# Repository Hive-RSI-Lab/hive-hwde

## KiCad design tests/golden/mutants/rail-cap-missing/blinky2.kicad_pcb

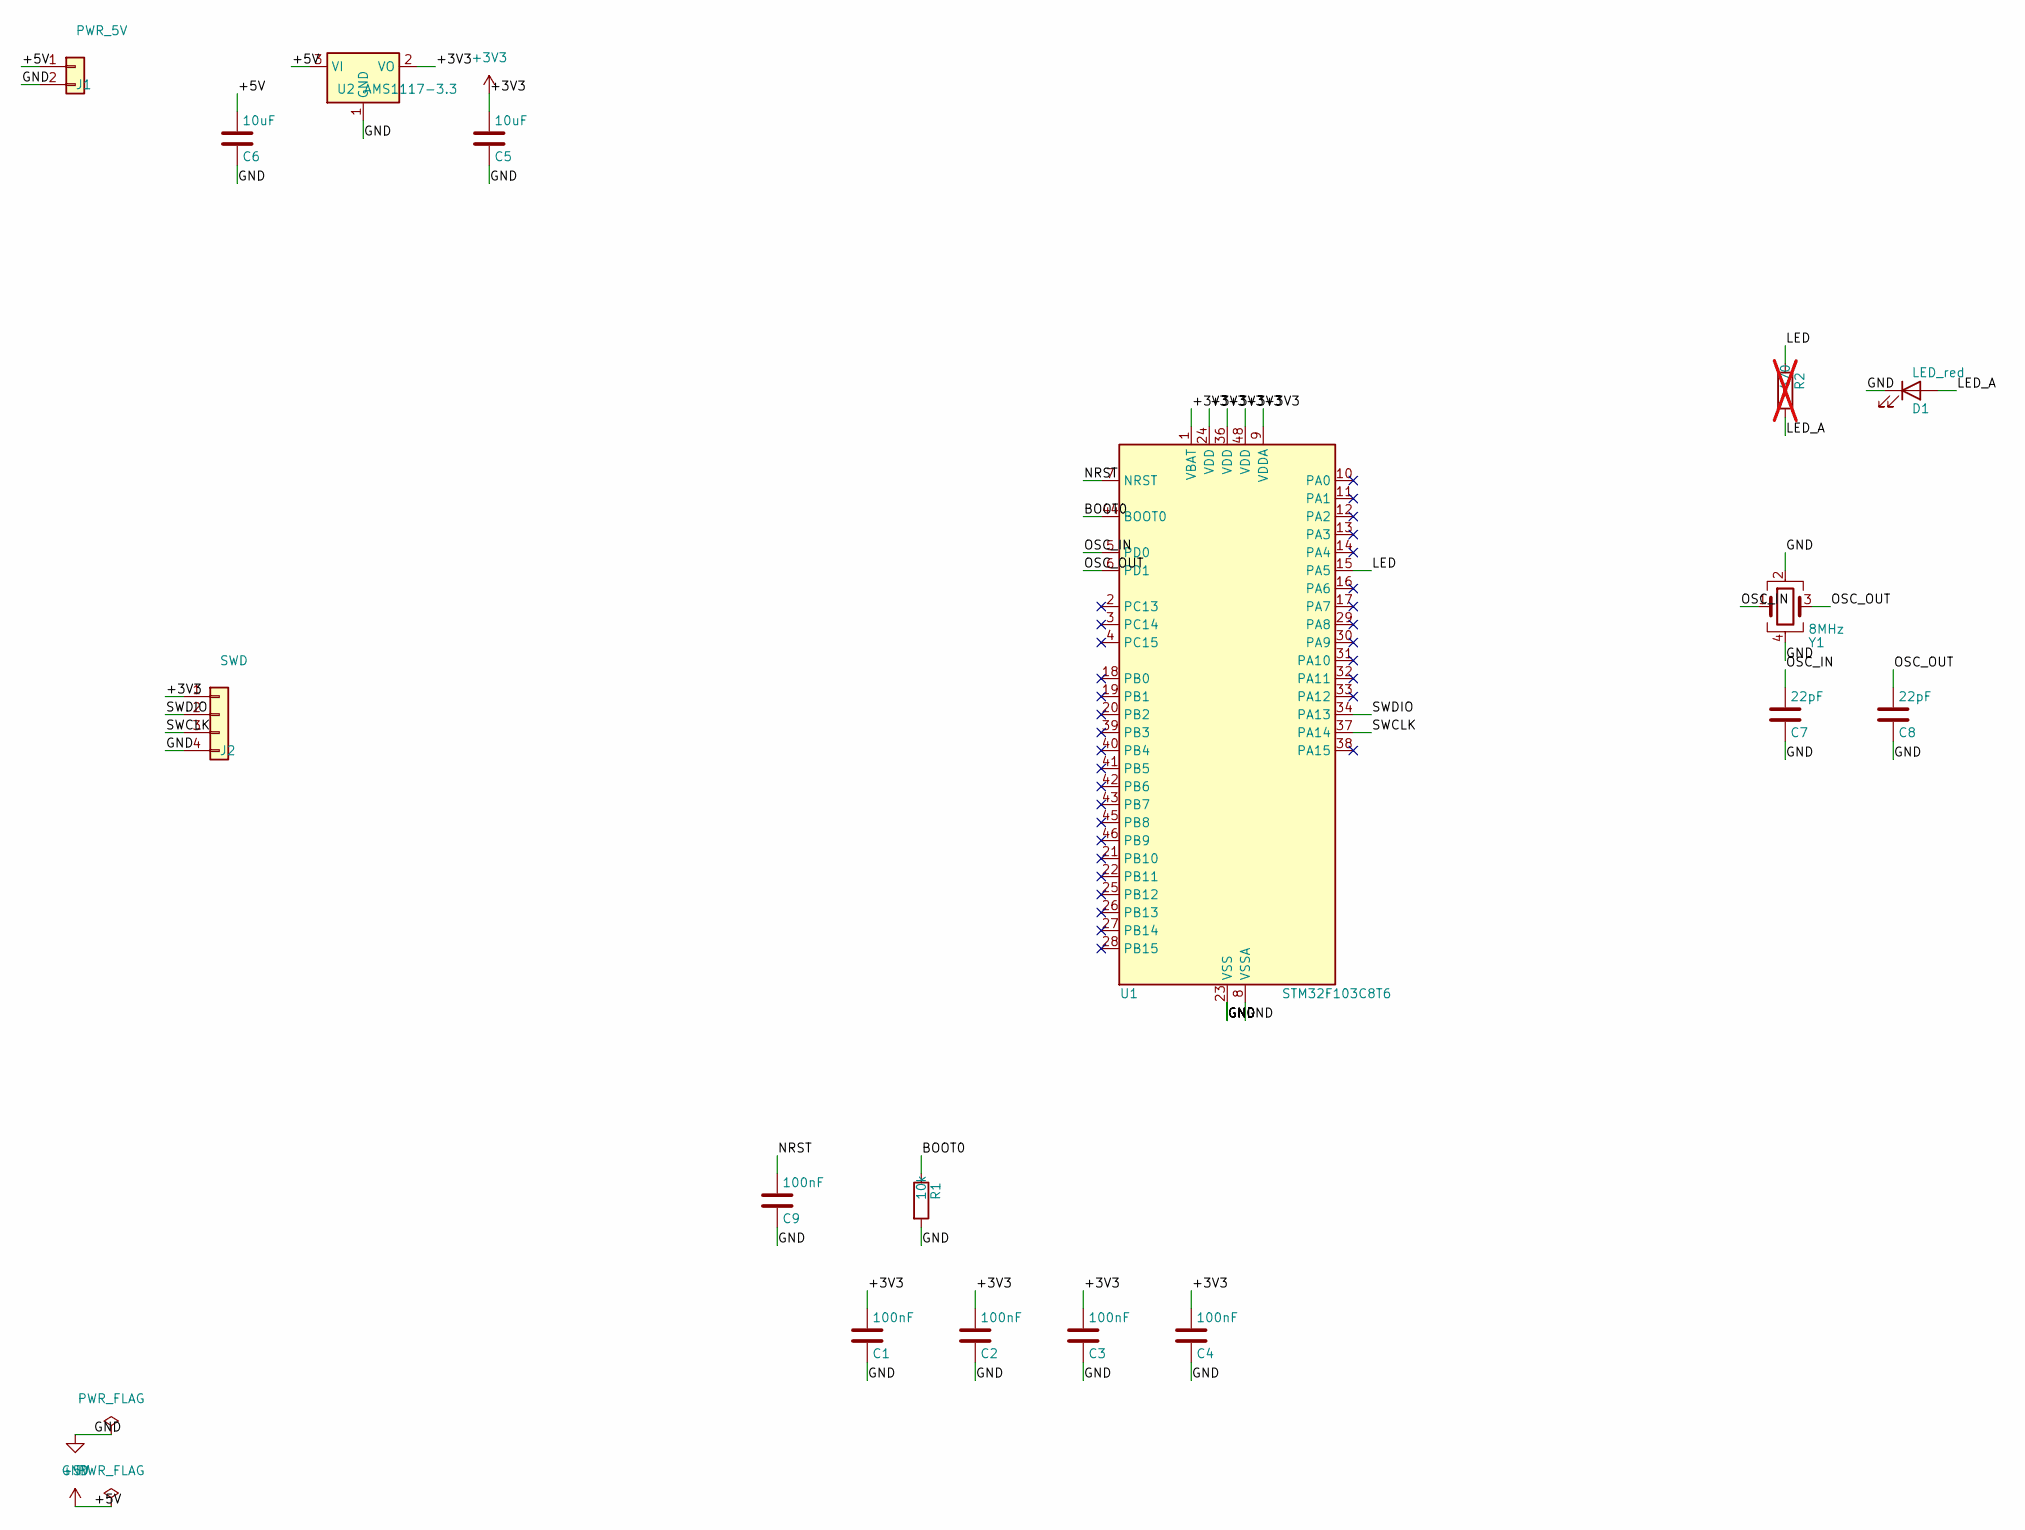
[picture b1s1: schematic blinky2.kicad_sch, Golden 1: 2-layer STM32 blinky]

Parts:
C1, C2, C3, C4, C9: 100nF; C_0603_1608Metric
C5, C6: 10uF; C_0805_2012Metric
C7, C8: 22pF; C_0603_1608Metric
D1: LED_red; LED_0805_2012Metric
J1: PWR_5V; PinHeader_1x02_P2.54mm_Vertical
J2: SWD; PinHeader_1x04_P2.54mm_Vertical
R1: 10k; R_0603_1608Metric
R2: 470; R_0603_1608Metric; not fitted
U1: STM32F103C8T6; LQFP-48_7x7mm_P0.5mm
U2: AMS1117-3.3; SOT-223-3_TabPin2
Y1: 8MHz; Crystal_SMD_3225-4Pin_3.2x2.5mm

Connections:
+3V3: C1.1, C2.1, C3.1, C4.1, C5.1, J2.1, U1.1 (VBAT), U1.9 (VDDA), U1.24 (VDD), U1.36 (VDD), U1.48 (VDD), U2.2 (VO)
+5V: C6.1, J1.1, U2.3 (VI)
/BOOT0: R1.1, U1.44 (BOOT0)
/LED: R2.1, U1.15 (PA5)
/LED_A: D1.2 (A), R2.2
/NRST: C9.1, U1.7 (NRST)
/OSC_IN: C7.1, U1.5 (PD0), Y1.1
/OSC_OUT: C8.1, U1.6 (PD1), Y1.3
/SWCLK: J2.3, U1.37 (PA14)
/SWDIO: J2.2, U1.34 (PA13)
GND: C1.2, C2.2, C3.2, C4.2, C5.2, C6.2, C7.2, C8.2, C9.2, D1.1 (K), J1.2, J2.4, R1.2, U1.8 (VSSA), U1.23 (VSS), U1.35 (VSS), U1.47 (VSS), U2.1 (GND), Y1.2, Y1.4

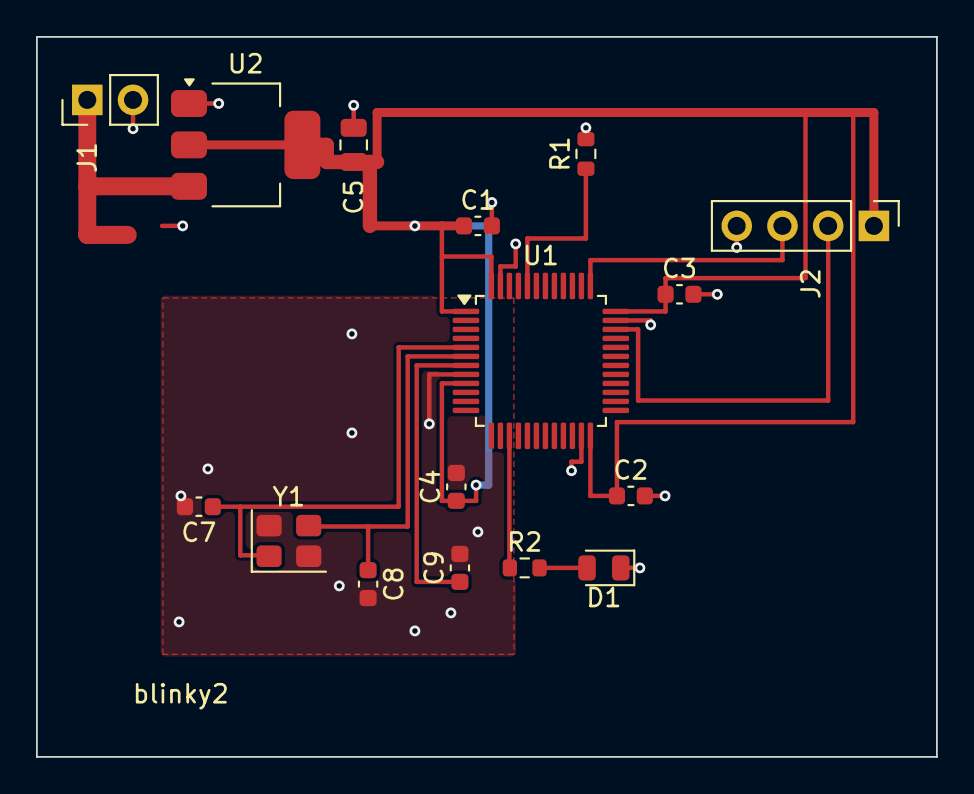
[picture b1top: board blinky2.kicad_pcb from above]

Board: 2 copper layers, 50.0 x 40.0 mm, 16 parts (0 on the bottom side), 11 nets.

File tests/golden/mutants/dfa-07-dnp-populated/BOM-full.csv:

Comment,Designator,Qty Per Board,Footprint,MPN,LCSC,Assembly Class,Instructions
PWR_5V,J1,1,PinHeader_1x02_P2.54mm_Vertical,,,smt_placed,
SWD,J2,1,PinHeader_1x04_P2.54mm_Vertical,,,smt_placed,
22pF,"C8,C7",2,C_0603_1608Metric,,,smt_placed,
10uF,"C5,C6",2,C_0805_2012Metric,,,smt_placed,
8MHz,Y1,1,Crystal_SMD_3225-4Pin_3.2x2.5mm,,,smt_placed,
100nF,"C9,C1,C2,C3,C4",5,C_0603_1608Metric,,,smt_placed,
10k,R1,1,R_0603_1608Metric,,,smt_placed,
STM32F103C8T6,U1,1,LQFP-48_7x7mm_P0.5mm,,,smt_placed,
AMS1117-3.3,U2,1,SOT-223-3_TabPin2,,,smt_placed,
470,R2,1,R_0603_1608Metric,,,smt_placed,
LED_red,D1,1,LED_0805_2012Metric,,,smt_placed,

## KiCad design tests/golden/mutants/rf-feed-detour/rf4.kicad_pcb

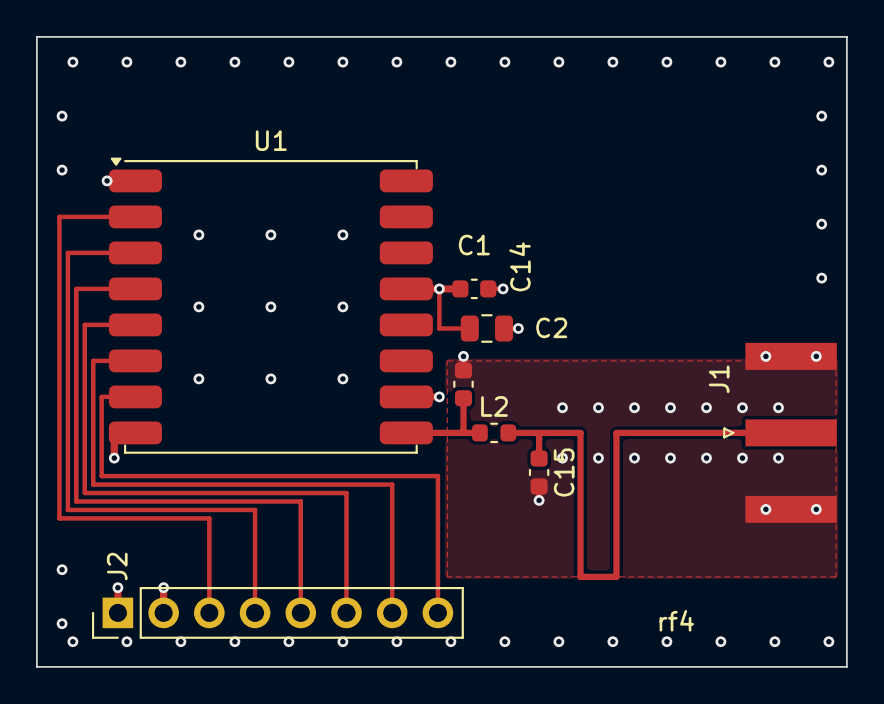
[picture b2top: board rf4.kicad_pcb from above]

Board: 4 copper layers, 45.0 x 35.0 mm, 8 parts (0 on the bottom side), 10 nets.

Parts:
C1: 100nF; C_0603_1608Metric
C2: 10uF; C_0805_2012Metric
C14: 5.6pF; C_0603_1608Metric
C15: 8.2pF; C_0603_1608Metric
J1: SMA; SMA_Amphenol_132289_EdgeMount
J2: SPI; PinHeader_1x08_P2.54mm_Vertical
L2: 6.8nH; L_0603_1608Metric
U1: RFM95W-868S2; HOPERF_RFM9XW_SMD

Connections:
+3V3: C1.1, C2.1, J2.1, U1.13
/DIO5: J2.8, U1.7
/MISO: J2.3, U1.2
/MOSI: J2.4, U1.3
/NSS: J2.6, U1.5
/RESET: J2.7, U1.6
/RF1: C14.1, L2.1, U1.9
/RF_FEED: C15.1, J1.1, L2.2
/SCK: J2.5, U1.4
GND: C1.2, C2.2, C14.2, C15.2, J1.2, J2.2, U1.1, U1.8, U1.10
